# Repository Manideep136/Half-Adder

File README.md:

# Half-Adder

## 📌 Project Overview

A **Half Adder** is a basic digital logic circuit used to perform the addition of two single-bit binary numbers. It produces two outputs:

* **Sum (S)**
* **Carry (C)**

The Half Adder is one of the fundamental building blocks used in digital electronics and forms the basic concept behind more complex arithmetic circuits such as **Full Adders, Binary Adders, and Arithmetic Logic Units (ALUs)**.

This project demonstrates the design and implementation of a Half Adder circuit using logic gates and a PCB designed using **KiCad**.

---

## 🎯 Objectives

* To understand the basic operation of binary addition.
* To design a Half Adder using digital logic gates.
* To implement the Sum and Carry logic.
* To create the circuit schematic using KiCad.
* To design a PCB layout for the circuit.
* To understand the relationship between logic gates and binary arithmetic.

---

## ⚙️ Working Principle

A Half Adder accepts two binary inputs:

* **A** – First input bit
* **B** – Second input bit

It produces:

* **Sum (S)** – Result of binary addition
* **Carry (C)** – Carry generated when both inputs are `1`

The Sum output is generated using an **XOR gate**, while the Carry output is generated using an **AND gate**.

### Boolean Expressions

```text
Sum = A XOR B

Carry = A AND B
```

Therefore, the circuit requires:

* 1 × XOR gate
* 1 × AND gate

---

## 🔢 Truth Table

| A | B | Sum | Carry |
| - | - | --- | ----- |
| 0 | 0 | 0   | 0     |
| 0 | 1 | 1   | 0     |
| 1 | 0 | 1   | 0     |
| 1 | 1 | 0   | 1     |

### Explanation

* **0 + 0 = 00** → Sum = 0, Carry = 0
* **0 + 1 = 01** → Sum = 1, Carry = 0
* **1 + 0 = 01** → Sum = 1, Carry = 0
* **1 + 1 = 10** → Sum = 0, Carry = 1

---

## 🧩 Components Required

| Component             |    Quantity | Purpose                 |
| --------------------- | ----------: | ----------------------- |
| XOR Gate IC           |           1 | Generates Sum           |
| AND Gate IC           |           1 | Generates Carry         |
| LED                   |           2 | Indicates Sum and Carry |
| Resistors             |           2 | Limits LED current      |
| Push Buttons/Switches |           2 | Provides inputs A and B |
| Breadboard/PCB        |           1 | Circuit implementation  |
| Connecting Wires      | As required | Electrical connections  |
| Power Supply          |           1 | Provides circuit power  |

### Example ICs

For a 74-series implementation, commonly used ICs include:

* **74LS86** – Quad 2-Input XOR Gate
* **74LS08** – Quad 2-Input AND Gate

---

## 🔌 Circuit Operation

The two input switches provide binary values **A** and **B**.

The inputs are connected simultaneously to the XOR and AND gates.

```text
             ┌─────────────┐
      A ─────┤             │
             │   XOR Gate  ├──── Sum
      B ─────┤             │
             └─────────────┘

             ┌─────────────┐
      A ─────┤             │
             │   AND Gate  ├──── Carry
      B ─────┤             │
             └─────────────┘
```

When the inputs are different, the XOR gate produces a `1`, so the **Sum LED turns ON**.

When both inputs are `1`, the AND gate produces a `1`, so the **Carry LED turns ON**.

---

## 🖥️ KiCad Design

The project can be designed using **KiCad** through the following stages:

1. Create a new KiCad project.
2. Draw the Half Adder schematic.
3. Add XOR and AND gate ICs.
4. Add input switches.
5. Add LEDs for Sum and Carry.
6. Add current-limiting resistors.
7. Connect the power supply and ground.
8. Assign appropriate footprints.
9. Create the PCB layout.
10. Run Electrical Rules Check (ERC).
11. Run Design Rules Check (DRC).
12. Generate the final PCB.

---

## 📐 PCB Design

The PCB contains the components required to implement the Half Adder circuit.

The board can include:

* Input terminals for **A and B**
* XOR gate IC
* AND gate IC
* Sum LED
* Carry LED
* Resistors
* Power and Ground terminals

Proper component placement and routing should be used to keep the PCB compact and easy to understand.

---

## 🧪 Testing

After assembling the PCB, the circuit can be tested by applying all possible combinations of the two inputs.

| Input A | Input B | Expected Sum | Expected Carry |
| ------- | ------- | ------------ | -------------- |
| OFF     | OFF     | OFF          | OFF            |
| OFF     | ON      | ON           | OFF            |
| ON      | OFF     | ON           | OFF            |
| ON      | ON      | OFF          | ON             |

The observed outputs should match the truth table.

---

## 📊 Applications

Half Adders are used as basic building blocks in:

* Binary arithmetic circuits
* Full Adders
* Arithmetic Logic Units (ALUs)
* Digital calculators
* Microprocessors
* Digital computers
* Counters and arithmetic circuits
* Digital signal processing systems

---

## ⚠️ Limitations

A Half Adder can add only **two single-bit binary numbers**. It does not have a **Carry-In** input.

Therefore, it cannot directly add multiple-bit binary numbers where a carry from a previous bit needs to be considered. For this purpose, a **Full Adder** is used.

---

## 🚀 Future Improvements

The project can be extended by:

* Designing a **Full Adder**.
* Combining multiple Full Adders to create a multi-bit binary adder.
* Adding switches for easier input control.
* Adding a 7-segment display for output.
* Designing a compact PCB.
* Simulating the circuit before hardware implementation.

---

## 🛠️ Tools Used

* **KiCad** – Schematic and PCB Design
* **74LS86** – XOR Gate IC
* **74LS08** – AND Gate IC
* LEDs
* Resistors
* Push Buttons/Switches
* DC Power Supply

---

---

## 👨‍💻 Author

**Manideep**

Electronics and Communication Engineering (ECE)

---

## 📜 Conclusion

The Half Adder is a fundamental digital logic circuit that demonstrates how binary addition can be implemented using basic logic gates. In this project, an XOR gate is used to generate the **Sum**, while an AND gate generates the **Carry**. The circuit provides a simple and practical introduction to digital arithmetic and PCB design.

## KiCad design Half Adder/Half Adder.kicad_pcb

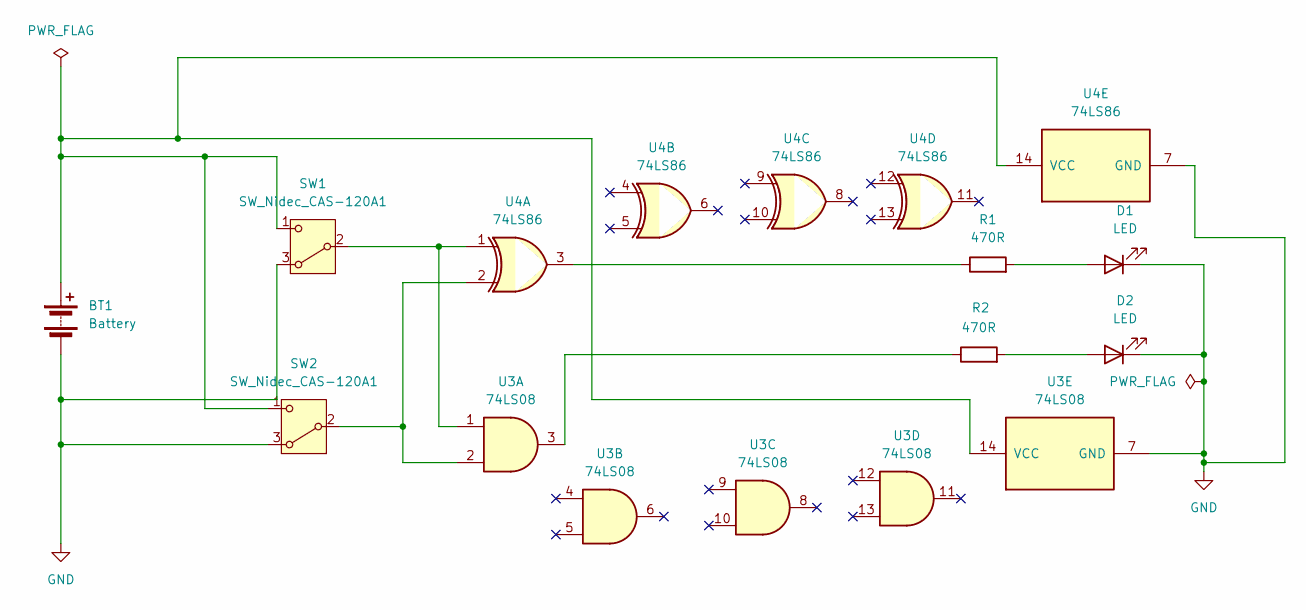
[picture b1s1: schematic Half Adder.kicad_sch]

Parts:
BT1: Battery; BatteryHolder_Bulgin_BX0123_1xCR123
D1, D2: LED; LED_D5.0mm
R1, R2: 470R; R_Axial_DIN0207_L6.3mm_D2.5mm_P10.16mm_Horizontal
SW1, SW2: SW_Nidec_CAS-120A1; Nidec_Copal_CAS-120A
U3: 74LS08; DIP-14_W7.62mm
U4: 74LS86; DIP-14_W7.62mm

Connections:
GND: BT1.2 (-), D1.1 (K), D2.1 (K), SW1.3 (A), SW2.3 (A), U3.7 (GND), U4.7 (GND)
unnamed: BT1.1 (+), SW1.1 (C), SW2.1 (C), U3.14 (VCC), U4.14 (VCC)
unnamed: D1.2 (A), R1.2
unnamed: D2.2 (A), R2.2
unnamed: R1.1, U4.3
unnamed: R2.1, U3.3
unnamed: SW1.2 (B), U3.1, U4.1
unnamed: SW2.2 (B), U3.2, U4.2

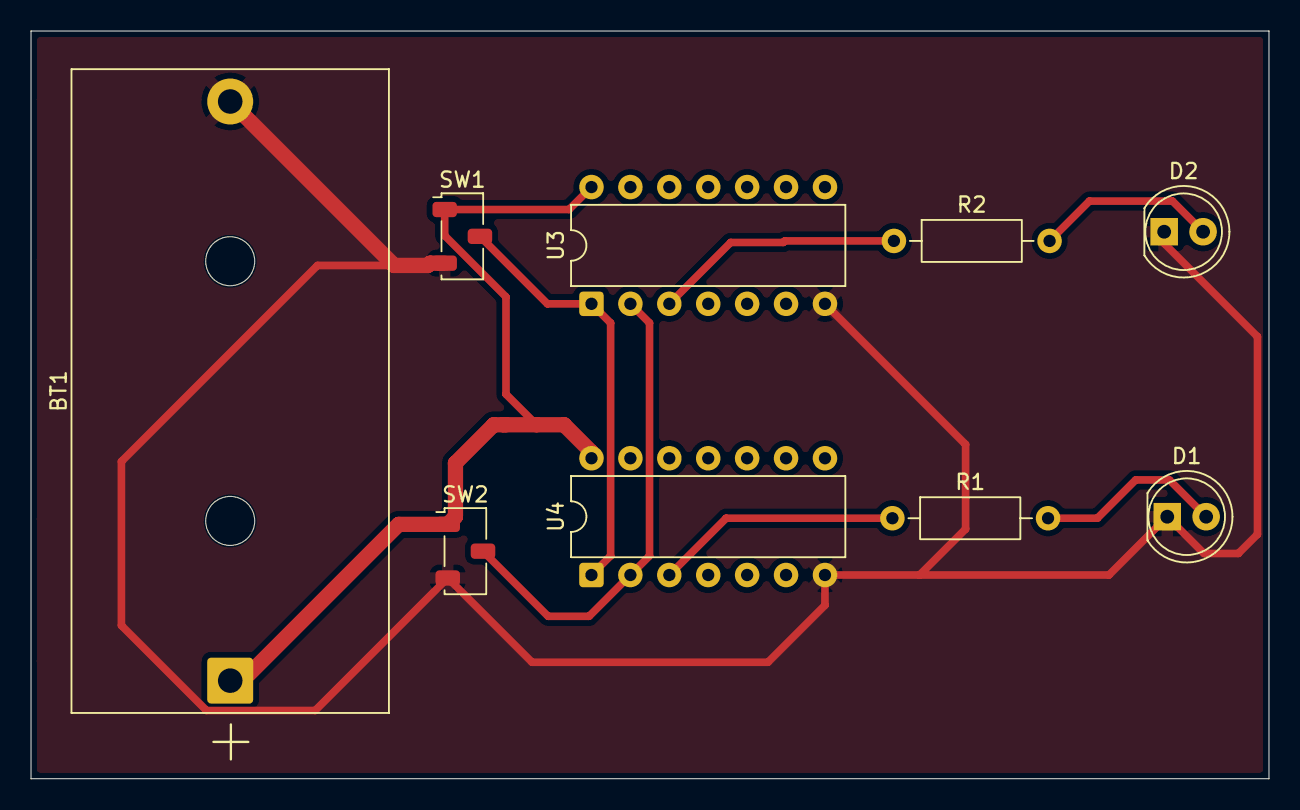
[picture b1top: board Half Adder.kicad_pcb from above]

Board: 2 copper layers, 80.8 x 48.8 mm, 9 parts (0 on the bottom side), 8 nets.
